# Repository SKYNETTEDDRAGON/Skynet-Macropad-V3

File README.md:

# Skynet-Macropad-V3
My first ever macropad :)

#Overview:
- I love drawing and making things on my computer, be it video games (my fav), systems, or drawing on procreate. I wanted a shortcut keyboard of some kind since forever - at the time I didn't know the name - and eventually when I first joined HackClub I found Blueprint, which showed me an awesome tutorial on how to build a macropad. Since I had never touched a PCB, much less built one, I decided to challenge myself into stepping into the world of hardware. Hence, my first ever macropad!  

##PCB:
I wanted to make a sipler version of a macropad sicne this is my first ever hardware project, hence I stuck to only adding 2 extra keys (6 keys in total) to my project. Here is the schematic:  (sorry if it's a bit messy)
and here's my schematic: 

##CAD:

Here's a pic of how everything in my design fits together: 

##Firmware:

Since my design for the whole keyboard itself wasn't too complex, my code wasn't either. While I initially suffered with my computer not being able to compile basic python, I eventually was able to make it do so, and FINALLY run the code properly.

##BOM:

- 4 M3x16mm screws
- 6 Blank DSA black keycaps
- 6 MX-Style switches
- 1 Seeed XIAO RP2040

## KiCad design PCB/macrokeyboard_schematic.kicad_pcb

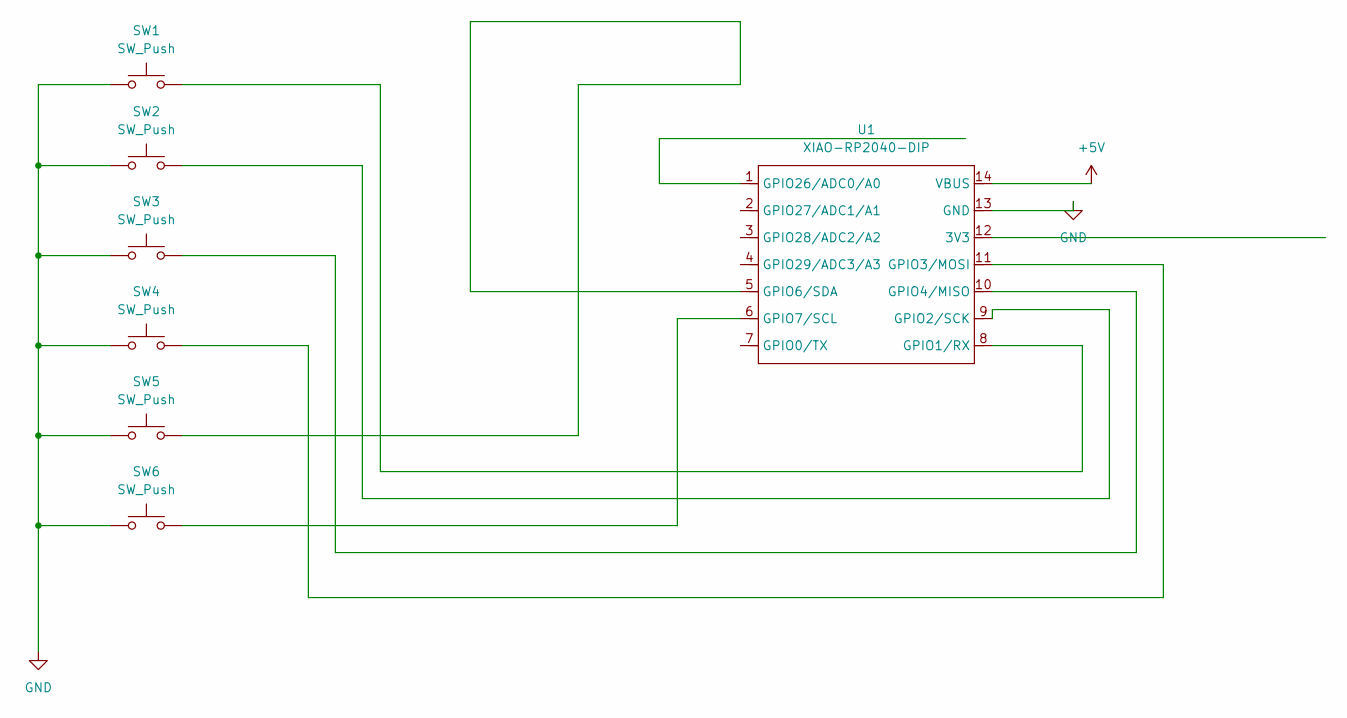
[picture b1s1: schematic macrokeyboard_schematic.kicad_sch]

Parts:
SW1, SW2, SW3, SW4, SW5, SW6: SW_Push; SW_Cherry_MX_1.00u_PCB
U1: XIAO-RP2040-DIP

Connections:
+5V: U1.14 (VBUS)
GND: SW1.1, SW2.1, SW3.1, SW4.1, SW5.1, SW6.1, U1.13 (GND)
unnamed: SW1.2, U1.8 (GPIO1/RX)
unnamed: SW2.2, U1.9 (GPIO2/SCK)
unnamed: SW4.2, U1.11 (GPIO3/MOSI)
unnamed: SW3.2, U1.10 (GPIO4/MISO)
unnamed: SW5.2, U1.5 (GPIO6/SDA)
unnamed: SW6.2, U1.6 (GPIO7/SCL)

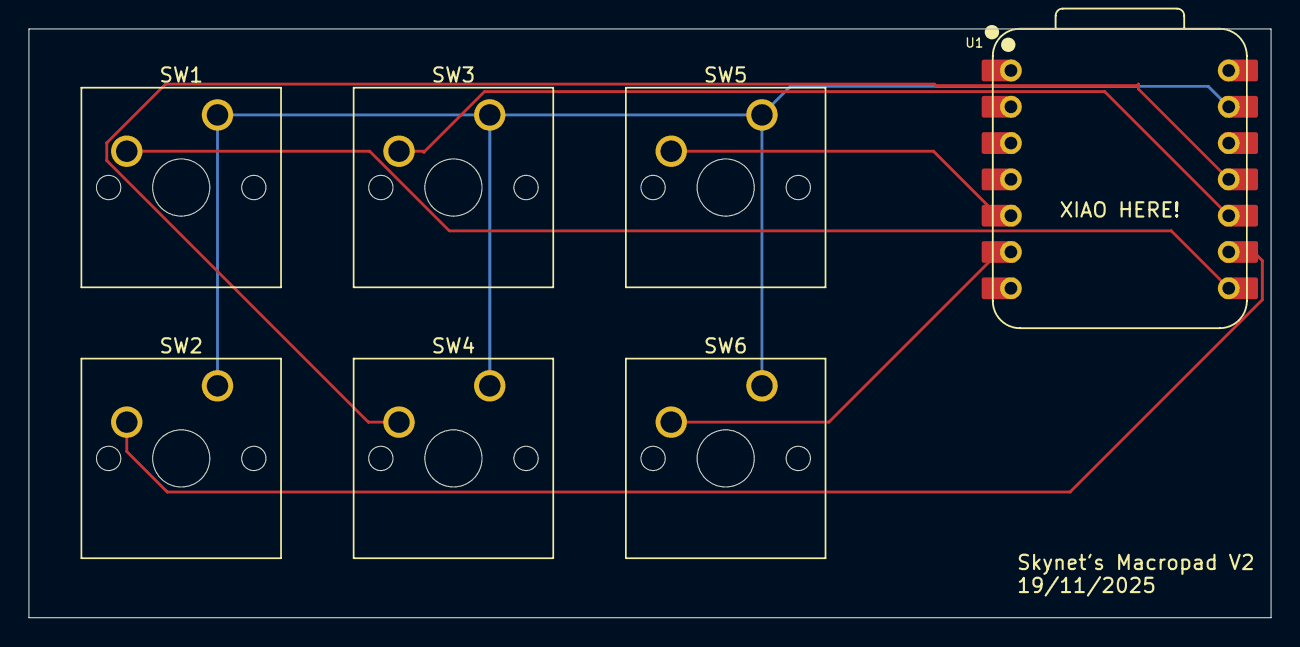
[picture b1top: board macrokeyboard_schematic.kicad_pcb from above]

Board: 2 copper layers, 86.9 x 41.2 mm, 7 parts (0 on the bottom side), 7 nets.

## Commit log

2025-11-23 init
2025-11-23 Create placeholder
